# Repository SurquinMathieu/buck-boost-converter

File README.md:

# Buck-Boost DC/DC Converter

A 4-switch synchronous buck-boost converter built around an STM32G431CBT6, with a digital PI control loop, USB CDC telemetry, and a real-time web dashboard for monitoring and control.

## Overview

This project implements a 4-switch buck-boost DC/DC converter. The STM32 runs a 300 kHz PWM control loop with real-time voltage sensing, feedforward + PI regulation, soft-start, and software UVLO protection. A companion web dashboard connects over USB to display live VIN/VOUT readings and lets you adjust the output setpoint from a browser.

**Key specifications**

| Parameter        | Value              |
|-------------------|-------------------|
| Input voltage     | 10 – 40 V          |
| Output voltage    | 3 – 15 V           |
| Max output current| 3 A                |
| Switching frequency | 300 kHz          |
| MCU               | STM32G431CBT6 (Cortex-M4, 170 MHz) |
| Topology          | 4-switch buck-boost |

## Features

- Digital PI control with feedforward
- Soft-start on power-up and on setpoint changes
- Software UVLO (on: 12 V, off: 10 V) backed by a hardware UVLO on the gate-driver supply
- Dual-simultaneous ADC sampling of VIN and VOUT, triggered by the timer
- USB CDC telemetry (VIN, VOUT, target, duty cycle)
- Web dashboard (Python/WebSocket backend + HTML/JS frontend) for live plotting and setpoint control
- State-machine firmware architecture designed to be extended to boost and full buck-boost modes

## Hardware

The converter uses four N-channel MOSFETs driven by two half-bridge gate drivers.

See [`hardware/kicad`](hardware/kicad) for the full KiCad project and [`hardware/bom`](hardware/bom) for the bill of materials.

## Firmware

See [`firmware/`](firmware) for the STM32CubeIDE project.

### Building

1. Open the project in STM32CubeIDE (`firmware/DC-DC-Converter.ioc`)
2. Build and flash to an STM32G431CBT6
3. Connect over USB

## Dashboard

The dashboard connects to the board's virtual COM port and streams VIN/VOUT/target data to a browser in real time over a local WebSocket, with a live waveform plot and a setpoint control.

### Running it

```bash
cd dashboard
pip install pyserial websockets
python server.py
```

Then open `index.html` in a browser. Update the `PORT` variable in `server.py` to match your board's COM port.

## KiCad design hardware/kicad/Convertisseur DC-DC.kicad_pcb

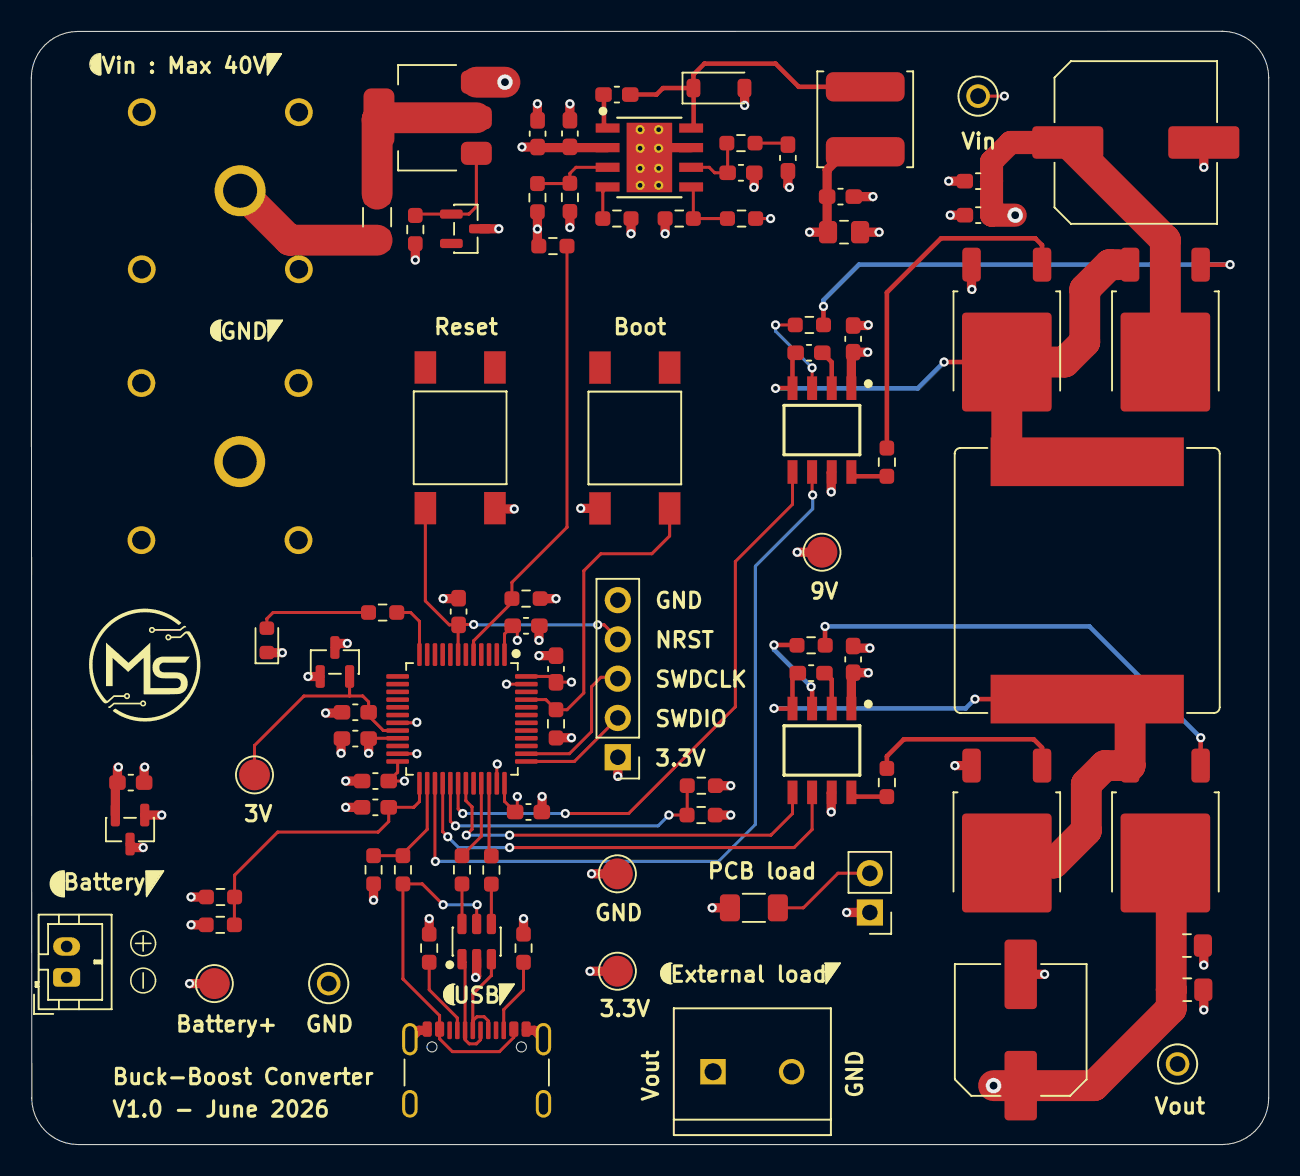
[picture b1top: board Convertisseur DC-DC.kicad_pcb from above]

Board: 4 copper layers, 80.0 x 72.0 mm, 87 parts (0 on the bottom side), 53 nets.

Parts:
C1: 560pF; C_0603_1608Metric_Pad1.08x0.95mm_HandSolder
C2, C3, C4, C5, C6, C7, C8, C9, C10, C11, C12, C13, C14, C15, C16, C17: 0.1uF; C_0603_1608Metric_Pad1.08x0.95mm_HandSolder
C18: 330nF; C_0603_1608Metric_Pad1.08x0.95mm_HandSolder
C19: 1uF; C_0603_1608Metric_Pad1.08x0.95mm_HandSolder
C20, C21: 2.2uF; C_0603_1608Metric_Pad1.08x0.95mm_HandSolder
C22, C23, C24: 10uF; C_0805_2012Metric_Pad1.18x1.45mm_HandSolder
C25: 100uF; C_Elec_10x10.2
C26: 220uF; C_Elec_8x10.2
D1: BZX84C10; SOT-23
D2: 150060SS75000; LED_0603_1608Metric
D3: RB162MM-60TR; D_SOD-123
D4: USBLC6-2SC6; SOT-23-6
F1: 0685T6000-01; Fuse_1206_3216Metric_Pad1.42x1.75mm_HandSolder
J1: FCR7350R; FCR7350
J2: FCR7350B; FCR7350
J3: Conn_01x02; JST_PH_B2B-PH-K_1x02_P2.00mm_Vertical
J4: USB4105-GF-A; USB_C_Receptacle_GCT_USB4105-xx-A_16P_TopMnt_Horizontal
J5: Conn_01x02; PinHeader_1x02_P2.54mm_Vertical
J6: Screw_Terminal_01x02; TE_282837-2
J7: Conn_01x05; PinHeader_1x05_P2.54mm_Vertical
L1: 15uH; L_TDK_VLS6045EX_VLS6045AF
L2: 39uH; L_Bourns_SRP1770TA_16.9x16.9mm
Q1, Q2, Q3, Q4: IPD053N06NATMA1; TO-252-2
Q5: DMP6023LE-13; SOT-223-3_TabPin2
R1, R2, R3, R4: 4.7R; R_0603_1608Metric_Pad0.98x0.95mm_HandSolder
R5, R6: 22R; R_0603_1608Metric_Pad0.98x0.95mm_HandSolder
R7: 68R; R_0603_1608Metric_Pad0.98x0.95mm_HandSolder
R8: 1k; R_1206_3216Metric_Pad1.30x1.75mm_HandSolder
R9: 1.4k; R_0603_1608Metric_Pad0.98x0.95mm_HandSolder
R10, R11: 5.1k; R_0603_1608Metric_Pad0.98x0.95mm_HandSolder
R12, R13, R14, R15: 10k; R_0603_1608Metric_Pad0.98x0.95mm_HandSolder
R16: 33k; R_0603_1608Metric_Pad0.98x0.95mm_HandSolder
R17: 40.2k; R_0603_1608Metric_Pad0.98x0.95mm_HandSolder
R18: 61.9k; R_0603_1608Metric_Pad0.98x0.95mm_HandSolder
R19: 68k; R_0603_1608Metric_Pad0.98x0.95mm_HandSolder
R20, R21: 100k; R_0603_1608Metric_Pad0.98x0.95mm_HandSolder
R22: 102k; R_0603_1608Metric_Pad0.98x0.95mm_HandSolder
R23: 124k; R_0603_1608Metric_Pad0.98x0.95mm_HandSolder
R24: 180k; R_0603_1608Metric_Pad0.98x0.95mm_HandSolder
R25: 249k; R_0603_1608Metric_Pad0.98x0.95mm_HandSolder
R26: 590k; R_0603_1608Metric_Pad0.98x0.95mm_HandSolder
SW1: Reset; SW_TS04-66-50-BK-260-SMT
SW2: Boot0; SW_TS04-66-50-BK-260-SMT
TP1: Vout; 5001
TP2: Vin; 5001
TP3: 9V; TestPoint_Pad_D2.0mm
TP4: 3V; TestPoint_Pad_D2.0mm
TP5: Vbatt; TestPoint_Pad_D2.0mm
TP6: GND; 5001
TP7: GND; TestPoint_Pad_D2.0mm
TP8: 3V3; TestPoint_Pad_D2.0mm
U1: STM32G431CBTx; LQFP-48_7x7mm_P0.5mm
U2: MCP1700T-3302ETT; SOT-23
U3: REF3030EAIDBZR; SOT-23
U4: TPS54360BDDAR; TI_SO-PowerPAD-8_ThermalVias
U5, U6: UCC27282DR

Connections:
+3.3V: C13.1, C14.1, C15.1, C16.1, C17.1, C19.1, J7.1, SW2.2, TP8.1, U1.1 (VBAT), U1.21 (VDDA), U1.24 (VDD), U1.36 (VDD), U1.48 (VDD), U2.2 (VO), U3.1 (IN)
+9V: C3.1, C4.1, C5.1, C22.1, L1.2, R22.1, TP3.1, U5.1 (VDD), U6.1 (VDD)
/Battery_V+: J3.2, R19.1, TP5.1, U2.3 (VI)
/Boot: R15.1, SW2.1, U1.45 (PB8)
/HO_Q1_G: Q1.1 (G), R1.2
/HO_Q3_G: Q3.1 (G), R3.2
/LED: R7.1, U1.12 (PA4)
/LED_A: D2.2 (A), R7.2
/LO_Q2_G: Q2.1 (G), R2.2
/LO_Q4_G: Q4.1 (G), R4.2
/USB D+: R6.1, U1.34 (PA12)
/USB D-: R5.1, U1.33 (PA11)
/USBCC1: J4.A5 (CC1), R11.1
/USBCC2: J4.B5 (CC2), R10.1
/USBCD+: D4.3 (I/O2), J4.A6 (D+), J4.B6 (D+)
/USBCD-: D4.1 (I/O1), J4.A7 (D-), J4.B7 (D-)
/VBUS: D4.5 (VBUS), J4.A4 (VBUS), J4.A9 (VBUS), J4.B4 (VBUS), J4.B9 (VBUS), R20.1
/VREF+: C11.1, TP4.1, U1.20 (VREF+), U3.2 (OUT)
/Vin_Fused: F1.2, Q5.2 (D)
/Vin_Raw: F1.1, J1.1
/Vout_To_PCB_Load: J5.2, R8.1
GND: C1.2, C3.2, C4.2, C5.2, C6.2, C8.2, C10.2, C11.2, C12.2, C13.2, C14.2, C15.2, C16.2, C17.2, C18.2, C19.2, C20.2, C21.2, C22.2, C23.2, C24.2, C25.2, C26.2, D2.1 (K), D3.2 (A), D4.2 (GND), J2.1, J3.1, J4.A1 (GND), J4.A12 (GND), J4.B1 (GND), J4.B12 (GND), J4.S1 (SHIELD), J6.2, J7.5, Q2.3 (S), Q4.3 (S), R8.2, R10.2, R11.2, R12.2, R13.2, R14.2, R15.2, R16.2, R18.2, R21.2, R24.2, R25.2, SW1.1, TP6.1, TP7.1, U1.19 (VSSA), U1.23 (VSS), U1.35 (VSS), U1.47 (VSS), U2.1 (GND), U3.3 (GND), U4.7 (GND), U4.9 (GNDPAD), U5.7 (VSS), U6.7 (VSS)
HO_Q1: R1.1, U5.3 (HO)
HO_Q3: R3.1, U6.3 (HO)
LO_Q2: R2.1, U5.8 (LO)
LO_Q4: R4.1, U6.8 (LO)
NRST: C12.1, J7.4, SW1.2, U1.7 (PG10)
unnamed: C18.1, R9.2
unnamed: D1.1 (A), Q5.1 (G), R21.1
unnamed: C2.2, D3.1 (K), L1.1, U4.8 (SW)
unnamed: C2.1, U4.1 (BOOT)
unnamed: C1.1, R9.1, U4.6 (COMP)
unnamed: R18.1, R26.2, U4.3 (EN)
unnamed: R14.1, R22.2, U4.5 (FB)
unnamed: R25.1, U4.4 (RT/CLK)
unnamed: C7.1, U5.2 (HB)
unnamed: C9.1, U6.2 (HB)
PWM_HS_L: U1.30 (PA8), U5.5 (HI)
PWM_HS_R: U1.31 (PA9), U6.5 (HI)
PWM_LS_L: U1.27 (PB13), U5.6 (LI)
PWM_LS_R: U1.28 (PB14), U6.6 (LI)
SWDCLK: J7.3, U1.38 (PA14)
SWDIO: J7.2, U1.37 (PA13)
SW_L: C7.2, L2.1, Q1.3 (S), Q2.2 (D), U5.4 (HS)
SW_R: C9.2, L2.2, Q3.3 (S), Q4.2 (D), U6.4 (HS)
USB_Check: R16.1, R20.2, U1.26 (PB12)
USB_D+: D4.4 (I/O2), R6.2
USB_D-: D4.6 (I/O1), R5.2
Vbatt_To_ADC: C10.1, R19.2, R24.1, U1.25 (PB11)
Vin: C6.1, C8.1, C20.1, C21.1, C25.1, D1.3 (K), Q1.2 (D), Q5.3 (S), R23.1, R26.1, TP2.1, U4.2 (VIN)
Vin_To_ADC: R13.1, R23.2, U1.5 (PF0)
Vout: C23.1, C24.1, C26.1, J5.1, J6.1, Q3.2 (D), R17.1, TP1.1
Vout_To_ADC: R12.1, R17.2, U1.29 (PB15)

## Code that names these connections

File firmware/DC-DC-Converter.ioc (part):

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Mcu.Name=STM32G431C(6-8-B)Tx
Mcu.Package=LQFP48
Mcu.UserName=STM32G431C8Tx
PA11.Mode=Device
PA11.Signal=USB_DM
PA12.Mode=Device
PA12.Signal=USB_DP
PA4.Signal=GPIO_Output
PA8.Signal=S_TIM1_CH1
PA9.Signal=GPIO_Output
PB13.Mode=PWM Generation1 CH1 CH1N
PB13.Signal=TIM1_CH1N
PB14.Signal=GPIO_Output
PB15.Mode=IN15-Single-Ended
PB15.Signal=ADC2_IN15
PF0-OSC_IN.Mode=IN10-Single-Ended
PF0-OSC_IN.Signal=ADC1_IN10
RCC.HSE_VALUE=8000000
RCC.SYSCLKFreq_VALUE=170000000
RCC.SYSCLKSource=RCC_SYSCLKSOURCE_PLLCLK
board=custom
